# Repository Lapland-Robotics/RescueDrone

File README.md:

# RescueDrone
This application is a rescue drone (dji matrice 100) that automatic seeks a missing person and give a live support package if found

## division of tasks:
* Rasit
  * Automatic flying
  * people detection with (heat) camera
* Cederic
  * Batteries, component in the cold
  * Comunication with home base
  * home base application

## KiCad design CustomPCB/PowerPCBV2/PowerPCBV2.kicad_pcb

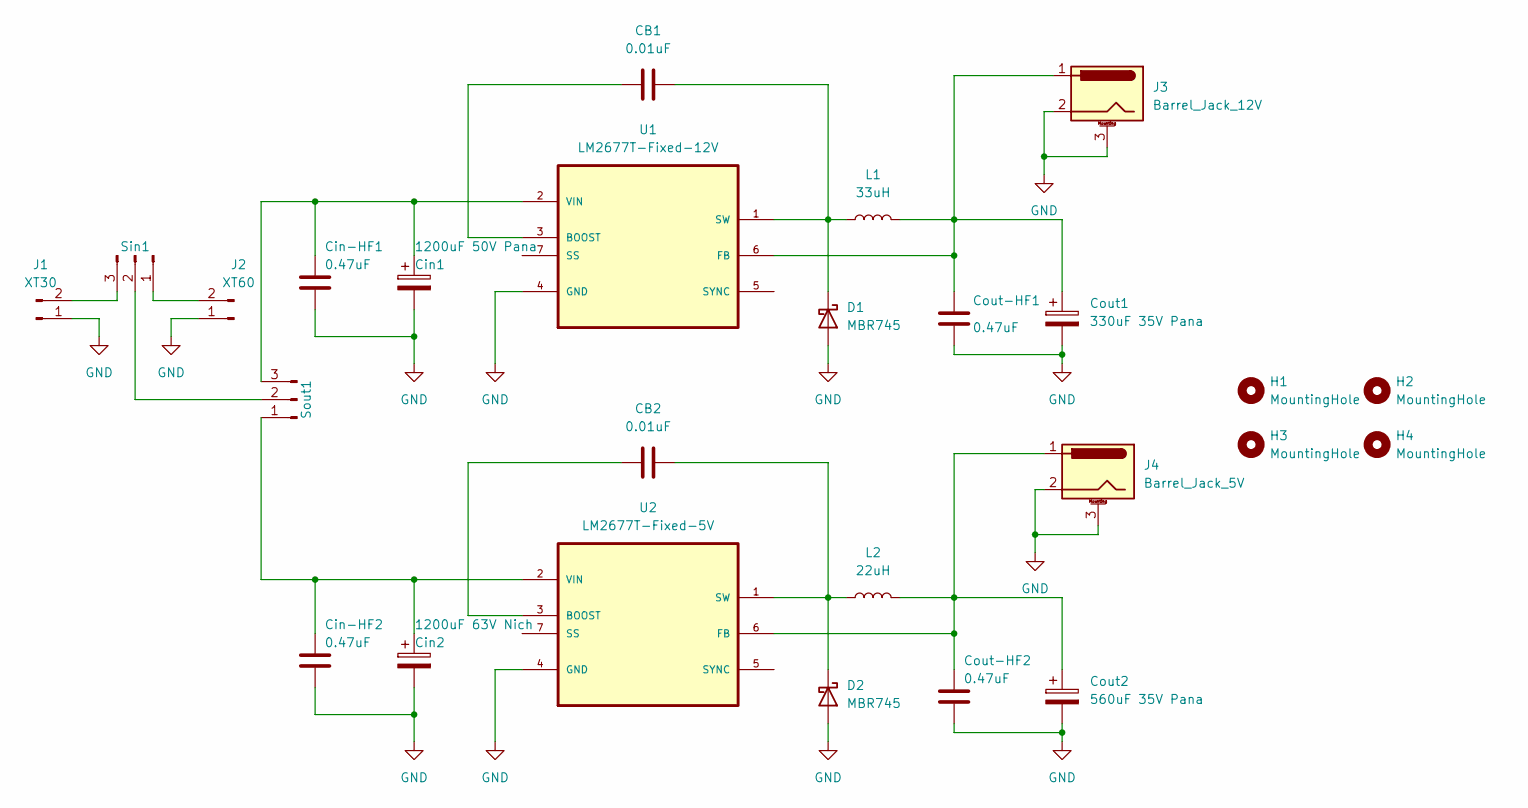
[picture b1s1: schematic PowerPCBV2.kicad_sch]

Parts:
CB1, CB2: 0.01uF; C_0805_2012Metric_Pad1.18x1.45mm_HandSolder
Cin1: 1200uF 50V Pana; CP_Radial_D16.0mm_P7.50mm
Cin2: 1200uF 63V Nich; CP_Radial_D18.0mm_P7.50mm
Cin-HF1, Cin-HF2: 0.47uF; C_0805_2012Metric_Pad1.18x1.45mm_HandSolder
Cout1: 330uF 35V Pana; CP_Radial_D10.0mm_P5.00mm
Cout2: 560uF 35V Pana; CP_Radial_D10.0mm_P5.00mm
Cout-HF1, Cout-HF2: 0.47uF; C_0805_2012Metric_Pad1.18x1.45mm_HandSolder
D1, D2: MBR745; TO-220-2_Vertical
H1, H2, H3, H4: MountingHole; MountingHole_2.5mm
J1: XT30; AMASS_XT30U-M_1x02_P5.0mm_Vertical
J2: XT60; AMASS_XT60-M_1x02_P7.20mm_Vertical
J3: Barrel_Jack_12V; BarrelJack_CUI_PJ-102AH_Horizontal_flat_pins
J4: Barrel_Jack_5V; BarrelJack_CUI_PJ-102AH_Horizontal_flat_pins
L1: 33uH; MGV1205-1207
L2: 22uH; MGV1205-1207
Sin1: Conn_01x03_Male; PinHeader_1x03_P2.54mm_Horizontal
Sout1: Conn_01x03_Male; PinHeader_1x03_P2.54mm_Horizontal
U1: LM2677T-Fixed-12V; TO127P457X1016X2052-7P; MPN LM2677T-ADJ
U2: LM2677T-Fixed-5V; TO127P457X1016X2052-7P; MPN LM2677T-ADJ

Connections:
GND: Cin1.2, Cin2.2, Cin-HF1.2, Cin-HF2.2, Cout1.2, Cout2.2, Cout-HF1.2, Cout-HF2.2, D1.2 (A), D2.2 (A), J1.1, J2.1, J3.2, J3.3, J4.2, J4.3, U1.4 (GND), U2.4 (GND)
unnamed: CB1.1, U1.3 (BOOST)
unnamed: CB1.2, D1.1 (K), L1.1, U1.1 (SW)
unnamed: CB2.1, U2.3 (BOOST)
unnamed: CB2.2, D2.1 (K), L2.1, U2.1 (SW)
unnamed: Cin1.1, Cin-HF1.1, Sout1.3, U1.2 (VIN)
unnamed: Cin2.1, Cin-HF2.1, Sout1.1, U2.2 (VIN)
unnamed: Cout1.1, Cout-HF1.1, J3.1, L1.2, U1.6 (FB)
unnamed: Cout2.1, Cout-HF2.1, J4.1, L2.2, U2.6 (FB)
unnamed: J1.2, Sin1.3
unnamed: J2.2, Sin1.1
unnamed: Sin1.2, Sout1.2

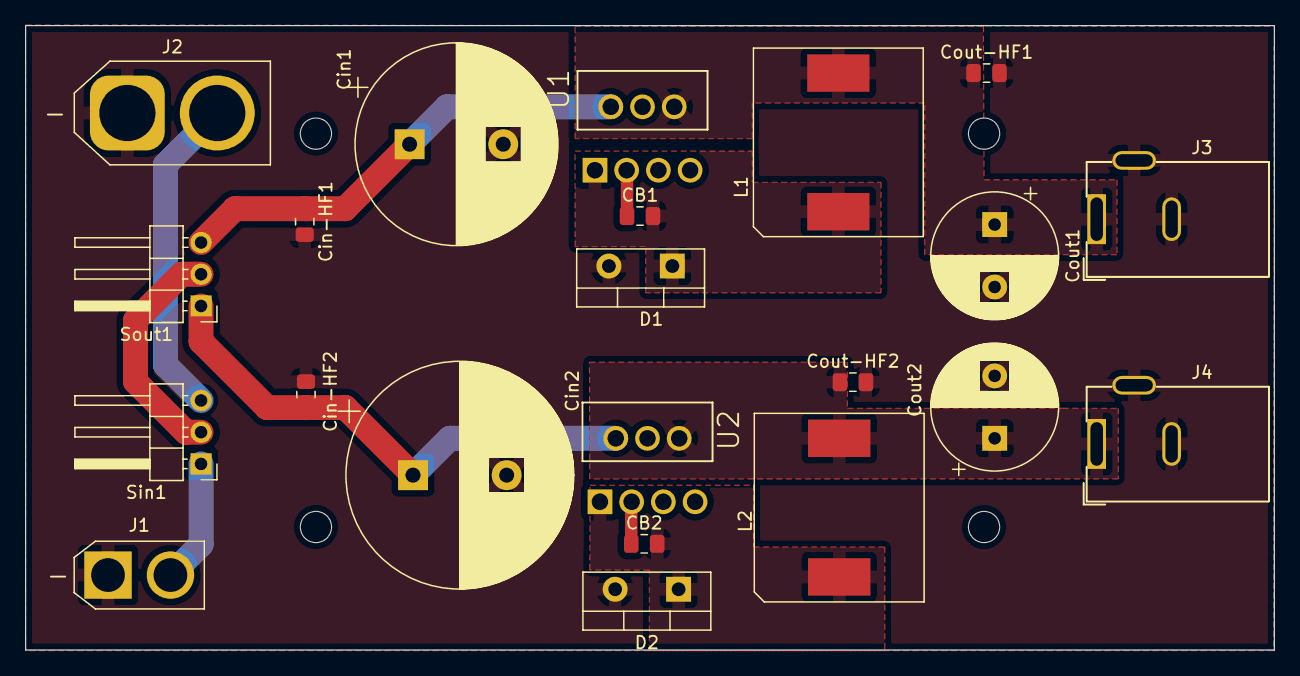
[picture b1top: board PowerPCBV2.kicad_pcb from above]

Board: 2 copper layers, 100.0 x 50.0 mm, 26 parts (0 on the bottom side), 12 nets.

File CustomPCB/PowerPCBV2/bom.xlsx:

Item | Qty one PCB | Reference(s) | value | Datasheet | multiple | qty to be orderd | link
Collated Components:
1 | 2 | CB1, CB2 | 0.01uF | 10nF cap | 3 | 6 | Digikey
2 | 4 | Cin-HF1, Cin-HF2, Cout-HF1, Cout-HF2 | 0,47uF | 470nF cap | 3 | 12 | Digikey
3 | 1 | Cin1 | 1200uF 50V Pana | Panasonic_FC-A | 3 | 3 | DigiKey
4 | 1 | Cin2 | 1200uF 63V Nich | Nich UPW | 3 | 3 | DigiKey
5 | 1 | Cout1 | 330uF 35V Pana | Panasonic_FR-A | 3 | 3 | Digikey
6 | 1 | Cout2 | 560uF 35V Pana | Panasonic_FR-A | 3 | 3 | Digikey
7 | 2 | D1, D2 | D_Schottky | MBR-745 | 3 | 6 | Digikey
8 | 1 | J1 | XT30 | XT30 | 0 | 0 | Digikey
9 | 1 | J2 | XT60 | XT60 | 0 | 0 | Digikey
10 | 1 | J3 | Barrel_Jack_12V | barrel Jack | 0 | 0 | Digikey
11 | 1 | J4 | Barrel_Jack_5V | barrel Jack | 0 | 0 | Digikey
12 | 1 | L1 | 33uH | MGV1207 | 3 | 3 | Digikey
13 | 1 | L2 | 22uH | MGV1207 | 3 | 3 | Digikey
14 | 2 | Sin1, Sout1 | Conn_01x03_Male | / | 0 | 0 | Digikey
15 | 1 | U1 | LM2677T-Fixed-12V | LM2677 | 3 | 3 | Digikey
16 | 1 | U2 | LM2677T-Fixed-5V | LM2677 | 3 | 3 | Digikey
Component Count: | 22 |  |  |  |  | 48

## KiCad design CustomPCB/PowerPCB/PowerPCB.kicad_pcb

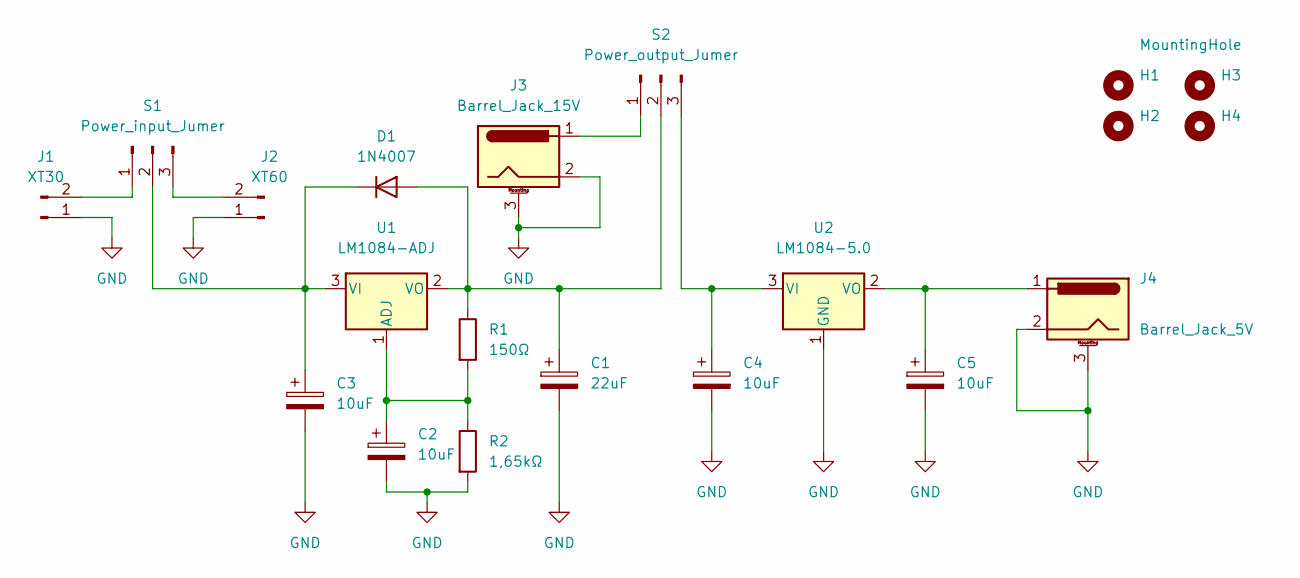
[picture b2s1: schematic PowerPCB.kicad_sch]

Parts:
C1: 22uF; CP_EIA-7343-31_Kemet-D
C2, C3, C4, C5: 10uF; CP_EIA-7343-31_Kemet-D
D1: 1N4007; D_DO-41_SOD81_P10.16mm_Horizontal
H1, H2, H3, H4: MountingHole; MountingHole_2.5mm
J1: XT30; AMASS_XT30U-M_1x02_P5.0mm_Vertical
J2: XT60; AMASS_XT60-M_1x02_P7.20mm_Vertical
J3: Barrel_Jack_15V; BarrelJack_CUI_PJ-102AH_Horizontal_flat_pins
J4: Barrel_Jack_5V; BarrelJack_CUI_PJ-102AH_Horizontal_flat_pins
R1: 150Ω; R_Axial_DIN0309_L9.0mm_D3.2mm_P12.70mm_Horizontal
R2: 1,65kΩ; R_Axial_DIN0309_L9.0mm_D3.2mm_P12.70mm_Horizontal
S1: Power_input_Jumer; PinHeader_1x03_P2.54mm_Horizontal
S2: Power_output_Jumer; PinHeader_1x03_P2.54mm_Horizontal
U1: LM1084-ADJ; TO-263-3_TabPin2
U2: LM1084-5.0; TO-263-3_TabPin2

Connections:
GND: C1.2, C2.2, C3.2, C4.2, C5.2, J1.1, J2.1, J3.2, J3.3, J4.2, J4.3, R2.2, U2.1 (GND)
unnamed: C1.1, D1.2 (A), R1.1, S2.2, U1.2 (VO)
unnamed: C2.1, R1.2, R2.1, U1.1 (ADJ)
unnamed: C3.1, D1.1 (K), S1.2, U1.3 (VI)
unnamed: C4.1, S2.3, U2.3 (VI)
unnamed: C5.1, J4.1, U2.2 (VO)
unnamed: J1.2, S1.1
unnamed: J2.2, S1.3
unnamed: J3.1, S2.1

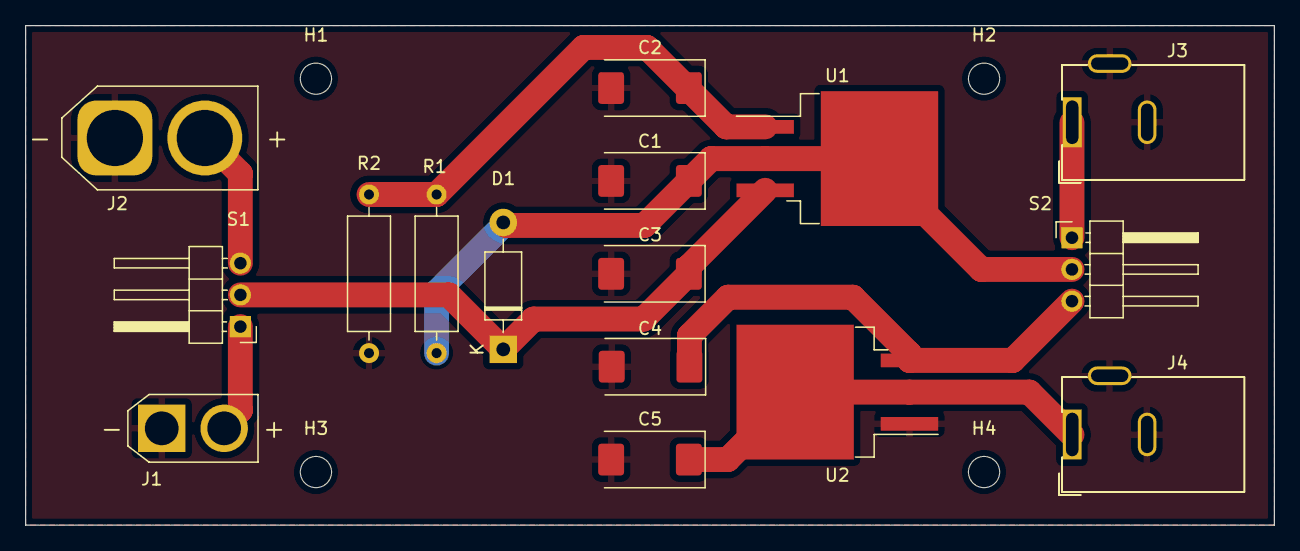
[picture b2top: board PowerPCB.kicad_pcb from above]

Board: 2 copper layers, 100.0 x 40.0 mm, 20 parts (0 on the bottom side), 9 nets.

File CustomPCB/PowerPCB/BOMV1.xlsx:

Component | Component number | Value | Quantity 1 PCB | Total (3 PCB) | Link
Voltage regulator | U1 | LM1084IS-ADJ | 1 | 3 | https://www.digikey.fi/en/products/detail/texas-instruments/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
 | U2 | LM1084IS-5.0 | 1 | 3 | https://www.digikey.fi/en/products/detail/texas-instruments/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
Diode | D1 | 1N4002 | 1 | 3 | (on campus)
Capacity (tantalums) | C2, C3, C4, C5 | 10uF | 4 | 12 | https://www.digikey.fi/en/products/detail/vishay-sprague/593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
 | C1 | 22uF | 1 | 3 | https://www.digikey.fi/en/products/detail/vishay-sprague/293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
Resistor | R1 | 150Ω | 1 | 3 | (on campus)
 | R2 | 1k65Ω | 1 | 3 | https://www.digikey.fi/en/products/detail/yageo/MFR50SFBE52-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
Connector | J1 | XT30 | 2 | 6 | https://www.digikey.fi/en/products/detail/dfrobot/FIT0586/9559255
 | J2 | XT60 | 2 | 6 | https://www.digikey.fi/en/products/detail/dfrobot/FIT0587/9559256
 | J3, j4 | Power jack | 2 | 6 | https://www.digikey.fi/en/products/detail/cui-devices/PJ-002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
Header Pin | S1, S2 | TLW-103-01-G-S-RA (5.2A per contact) | 2 | 6 | https://www.digikey.fi/en/products/detail/samtec-inc/TLW-103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
Jumper |  | 0015291027 (rated for 5A) | 2 | 6 | https://www.digikey.fi/en/products/detail/molex/0015291027/315123
Cable |  | 2.1 mm Barrel Plug | 1 | 1 | https://www.digikey.fi/en/products/detail/tensility-internat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
Total |  |  | 21 | 61

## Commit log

2022-02-16 Regulations
    #2
2022-02-16 first encounter wit ROS
    #1
2022-02-16 rem vid
2022-02-21 update file system
2022-02-21 starting drone API
    #13
2022-02-25 designing Power PCB
    #19
2022-02-25 costum pcb update
    #19
2022-03-01 gitignore update
2022-03-01 update PowerPCB
    #19
2022-03-01 costum mount
    #20
2022-03-01 redesign power pcb
    #23
2022-03-01 remove
2022-03-01 bom V2 update
    #23
2022-03-01 updates
    #23 #20
2022-03-15 update custom pcb and documentation
    #23
2022-03-15 MSDK example
    #34
2022-03-16 MSDK Activate SDK
    #34
2022-03-16 update git ignore
2022-03-16 MSDK
    #34
2022-03-22 MSDK First app
    #34
2022-03-23 update gitignore
    #34
2022-03-29 Human detection
    A very late github push.
2022-03-31 live heat camera
    This code streams the flir lepton 3.5 using opencv
2022-04-07 3D prints
    These documents containts the mounts we have made in order to mount the cameras underneath the drone.
2022-04-11 Update liveheatcamera.txt
    Live data readout + streaming
2022-04-12 Bodytemp
    Gives allert if more than 200 of the 19200 pixels are between 20 and 35 degrees Celcius
2022-04-14 ok
    ok
2022-04-19 all combined
2022-04-26 Create tmp
2022-04-26 test
2022-04-26 onboard computer code
2022-04-26 update git 26/04
2022-04-26 onboard computer code
    #47
2022-04-26 extension update
2022-04-29 Latest version
    program starts when receiving specific command
2022-04-29 add manual override and mobile callback funcions
2022-04-29 update MSDK install script and design propeller case
    #49 #51 #52
2022-05-03 Update rospd.py
    Added a feedback, where it goes back to body temperature if the AI can not detect a person(in case an animal was detected). The program is not able to reopen the IR camera, trying to fix that
2022-05-03 Done
    Demo version is completely done. The feedback function works as it is supposed to, the IR camera and the AI will keep switching between them until they are sure a person is detected. In case the dron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
2022-05-04 Update roshd.py
    Made it more friendly to use.
    Changes:
    +defined the commands so it will be easier to change it later on.
    +Implemented a function where the human detection only sends the data through ROS when it receives a 10 command from the drone itself.
2022-05-06 Update Onboard-computer #49
2022-05-10 Combining human detection and onboard computer #55 & #56
2022-05-10 Create routeplanner.py
    First version. The script is able to measure the distances between the points and calculate stop points on two sides that are opposite of each other. In this way, the drone will fly the surface of th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
2022-05-10 refining Movement #57
2022-05-11 implement area selecting + sound
    #48 #58
2022-05-13 Update routeplanner.py
    Still needs some work, weekly backup.
2022-05-16 Update routeplanner.py
    Just an update, not done. Trying to calculate variable x values so the area does not have to be a square every time.
2022-05-18 update with GPS and smooth movement #57
2022-05-18 implement area select and prevent crash #58
2022-05-24 Update routeplanner.py
    done, needs to be tested on unnatural cases and to be combined with ROS.
2022-05-27 update onboard-computer
2022-05-30 implement routeplanner #59
2022-05-31 Done without ROS
2022-05-31 implement routeplanner and go to start RTH #59
2022-06-01 final updates #60
2022-09-01 secret file
